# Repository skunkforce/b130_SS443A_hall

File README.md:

# edgy_board number b130
This design is part of the [edgy board project](https://github.com/skunkforce/edgy_boards). It provides the functionality of chip XXXX via interfaces YYYY. 

# getting started
This repository uses submodules. After cloning use the command 

```$ git submodule update --init --recursive```

to pull the submodules before opening the project with kicad. 

# Tests
Tests can be found in [TESTS.md](TESTS.md)

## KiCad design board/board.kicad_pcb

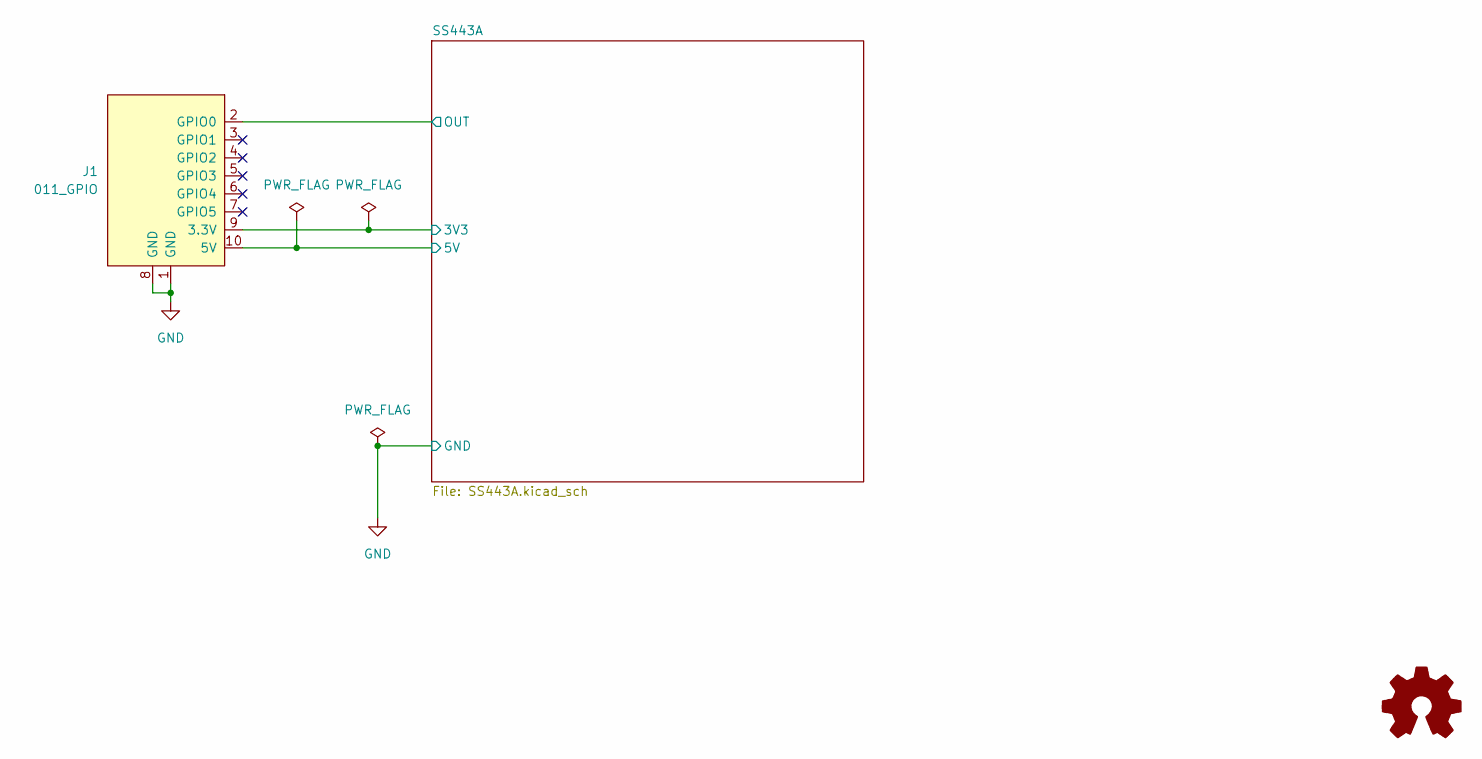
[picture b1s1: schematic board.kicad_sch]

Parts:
J1: 011_GPIO; on_edge_2x05_device
LOGO1: Logo_Open_Hardware_Small; OSHW-Symbol_6.7x6mm_SilkScreen

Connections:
/SS443A/3V3: J1.9 (3.3V); also elsewhere on the board
/SS443A/5V: J1.10 (5V); also elsewhere on the board
/SS443A/OUT: J1.2 (GPIO0); also elsewhere on the board
GND: J1.1 (GND), J1.8 (GND); also elsewhere on the board

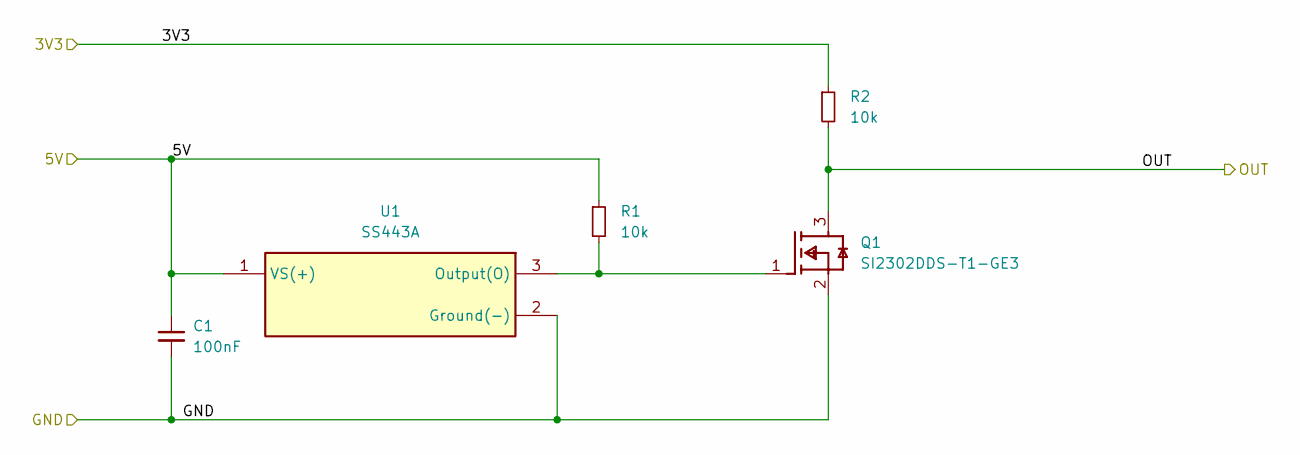
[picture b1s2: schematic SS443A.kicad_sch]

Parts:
C1: 100nF; C_0603_1608Metric_Pad1.08x0.95mm_HandSolder
Q1: SI2302DDS-T1-GE3; FP-S-03946-MFG
R1, R2: 10k; R_0603_1608Metric_Pad0.98x0.95mm_HandSolder
U1: SS443A; FP-SS443A-MFG

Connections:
/SS443A/3V3: R2.1; also elsewhere on the board
/SS443A/5V: C1.1, R1.1, U1.1 (VS(+)); also elsewhere on the board
/SS443A/OUT: Q1.3 (D), R2.2; also elsewhere on the board
GND: C1.2, Q1.2 (S), U1.2 (Ground(-)); also elsewhere on the board
unnamed: Q1.1 (G), R1.2, U1.3 (Output(O))

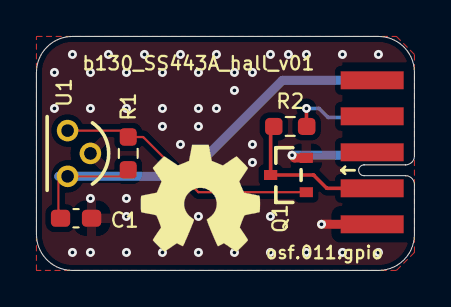
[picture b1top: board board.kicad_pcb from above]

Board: 2 copper layers, 21.0 x 13.0 mm, 7 parts (0 on the bottom side), 5 nets.

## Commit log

2023-05-10 Update libraries
